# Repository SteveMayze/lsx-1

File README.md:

# Leawood Sensor Adapter LSX-1

The Sensor Adapter is an adapter board that enables a USART-USB device and a UPDI ISP to be 
conected to a Leawood Sensor unit (i.e. LPS-1) via an RJ45 compatible cable. The RJ45 is used
for convenice and in no way will implement any TCP connection.

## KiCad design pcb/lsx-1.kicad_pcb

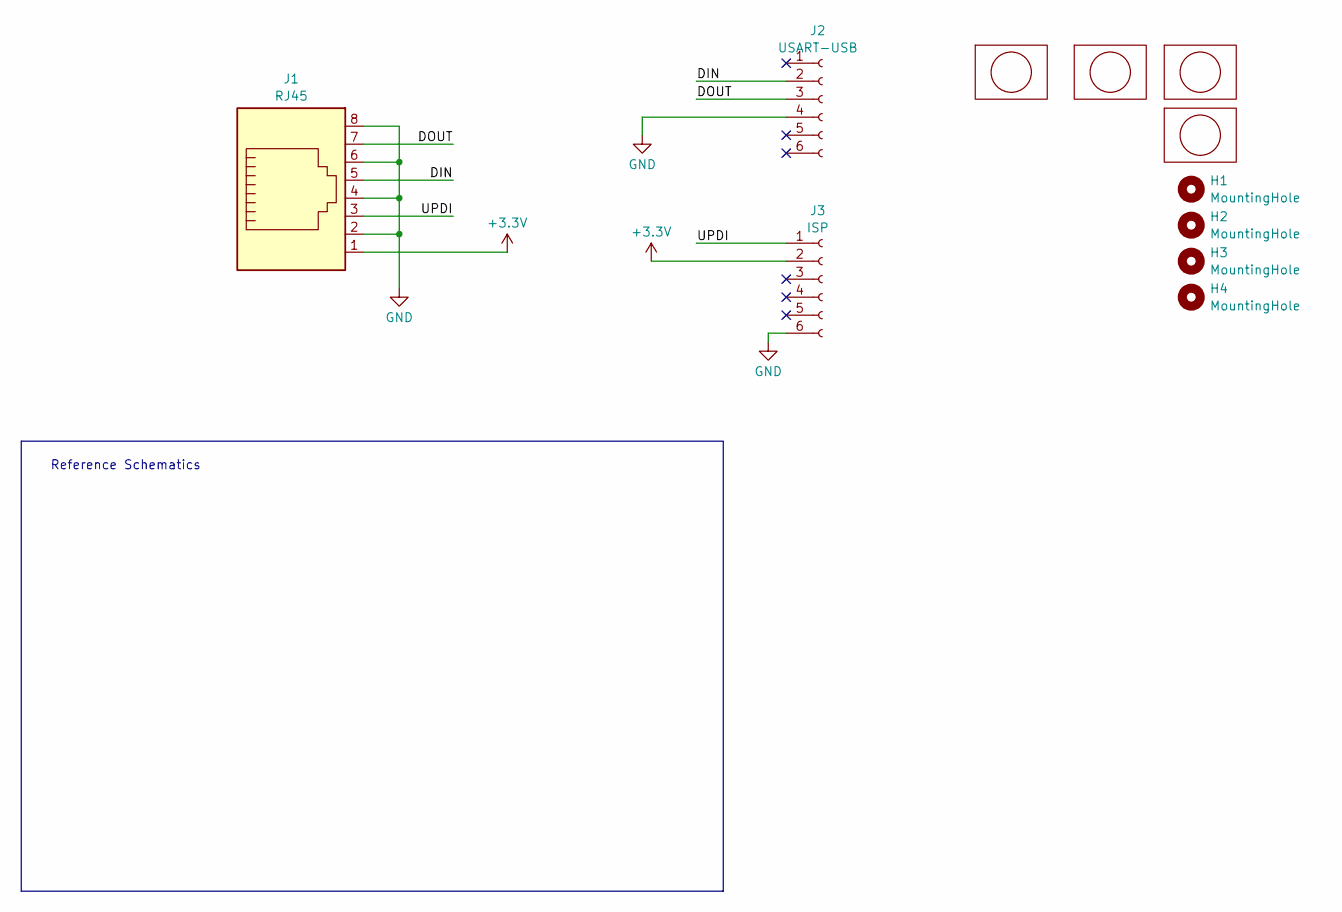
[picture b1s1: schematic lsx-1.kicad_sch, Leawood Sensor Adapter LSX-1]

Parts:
H1, H2, H3, H4: MountingHole; MountingHole_2.7mm_M2.5
J1: RJ45; RJ45_8P8C
J2: USART-USB; PinHeader_1x06_P2.54mm_Horizontal
J3: ISP; PinHeader_2x03_P2.54mm_Horizontal
Lg1: logo; MyBasic_rounded_50_1
Lg2: logo; KiCad-Logo_5mm_SilkScreen
Lg3, Lg4: logo; Non_TCP

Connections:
+3.3V: J1.1, J3.2
/DIN: J1.5, J2.2
/DOUT: J1.7, J2.3
/UPDI: J1.3, J3.1
GND: J1.2, J1.4, J1.6, J1.8, J2.4, J3.6

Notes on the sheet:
Reference Schematics

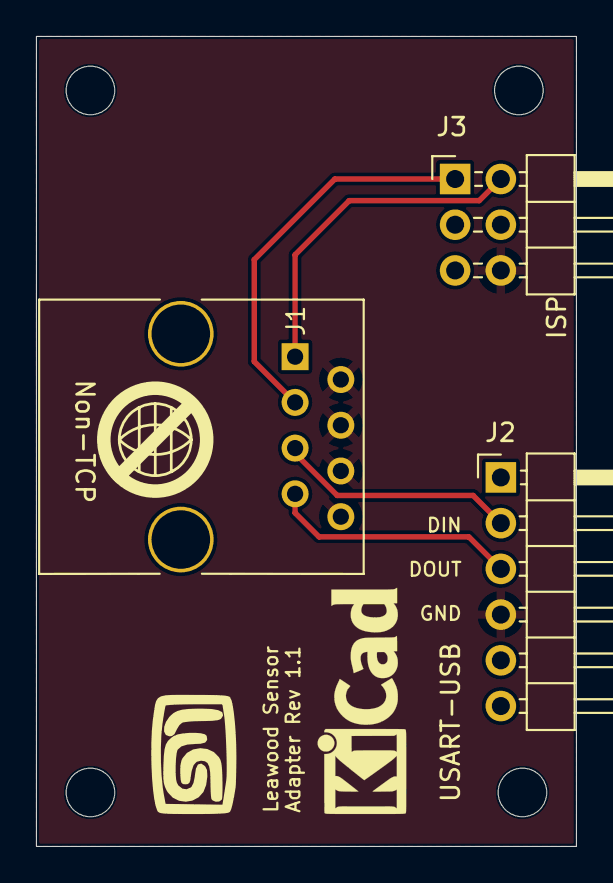
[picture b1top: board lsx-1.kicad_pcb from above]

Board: 2 copper layers, 30.0 x 45.0 mm, 11 parts (1 on the bottom side), 5 nets.

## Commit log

2024-03-27 Initial checkin of the design files
2024-05-12 Corrects the GND on the ISP
2024-11-03 Archived rev 1.1
2024-11-03 Starting to model the enclosure
